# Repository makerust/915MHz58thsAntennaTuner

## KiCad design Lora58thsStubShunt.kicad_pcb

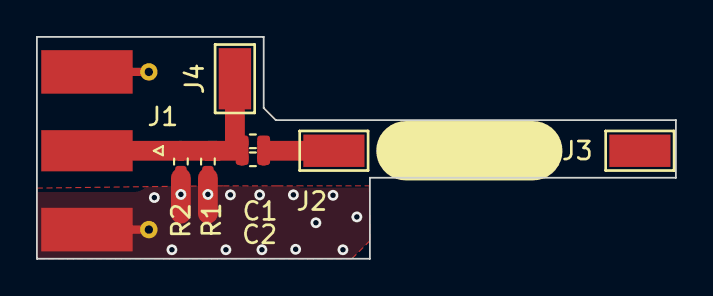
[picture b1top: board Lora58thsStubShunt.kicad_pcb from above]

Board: 2 copper layers, 35.5 x 12.3 mm, 8 parts (0 on the bottom side), 3 nets.

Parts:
C1, C2: C_Small; R_0402_1005Metric_Pad0.72x0.64mm_HandSolder
J1: Conn_Coaxial; SMA_Molex_73251-1153_EdgeMount_Horizontal
J2, J3, J4: Conn_01x01_Pin; TestPoint_Keystone_5015_Micro-Minature
R1: R60; R_0402_1005Metric_Pad0.72x0.64mm_HandSolder
R2: R5; R_0402_1005Metric_Pad0.72x0.64mm_HandSolder

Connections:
GND: J1.2 (Ext), R1.2, R2.2
unnamed: C1.1, C2.1, J1.1 (In), J4.1, R1.1, R2.1
unnamed: C1.2, C2.2, J2.1

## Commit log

2025-12-31 initial commit, chaotic features
2025-12-31 adds schematic
2026-01-01 Release Candidate
